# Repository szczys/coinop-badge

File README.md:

# coinop-badge

PCB badge inspired by the classic coin-op game Galaga

https://hackaday.io/project/159302/

# KiCAD Library dependencies

Install the KiCad libraries:
` sudo apt-get install kicad-library

Install the [https://github.com/MacroFab/EDALibraries](MacroFab EDALibraries):
` cd ~/compile
` git clone https://github.com/MacroFab/EDALibraries
` cd /usr/share/kicad/modules 
` sudo ln -s ~/compile/EDALibraries/KiCad/Footprints/* .
` cd /usr/share/kicad/library
` sudo ln -s ~/compile/EDALibraries/KiCad/Schematics/* .

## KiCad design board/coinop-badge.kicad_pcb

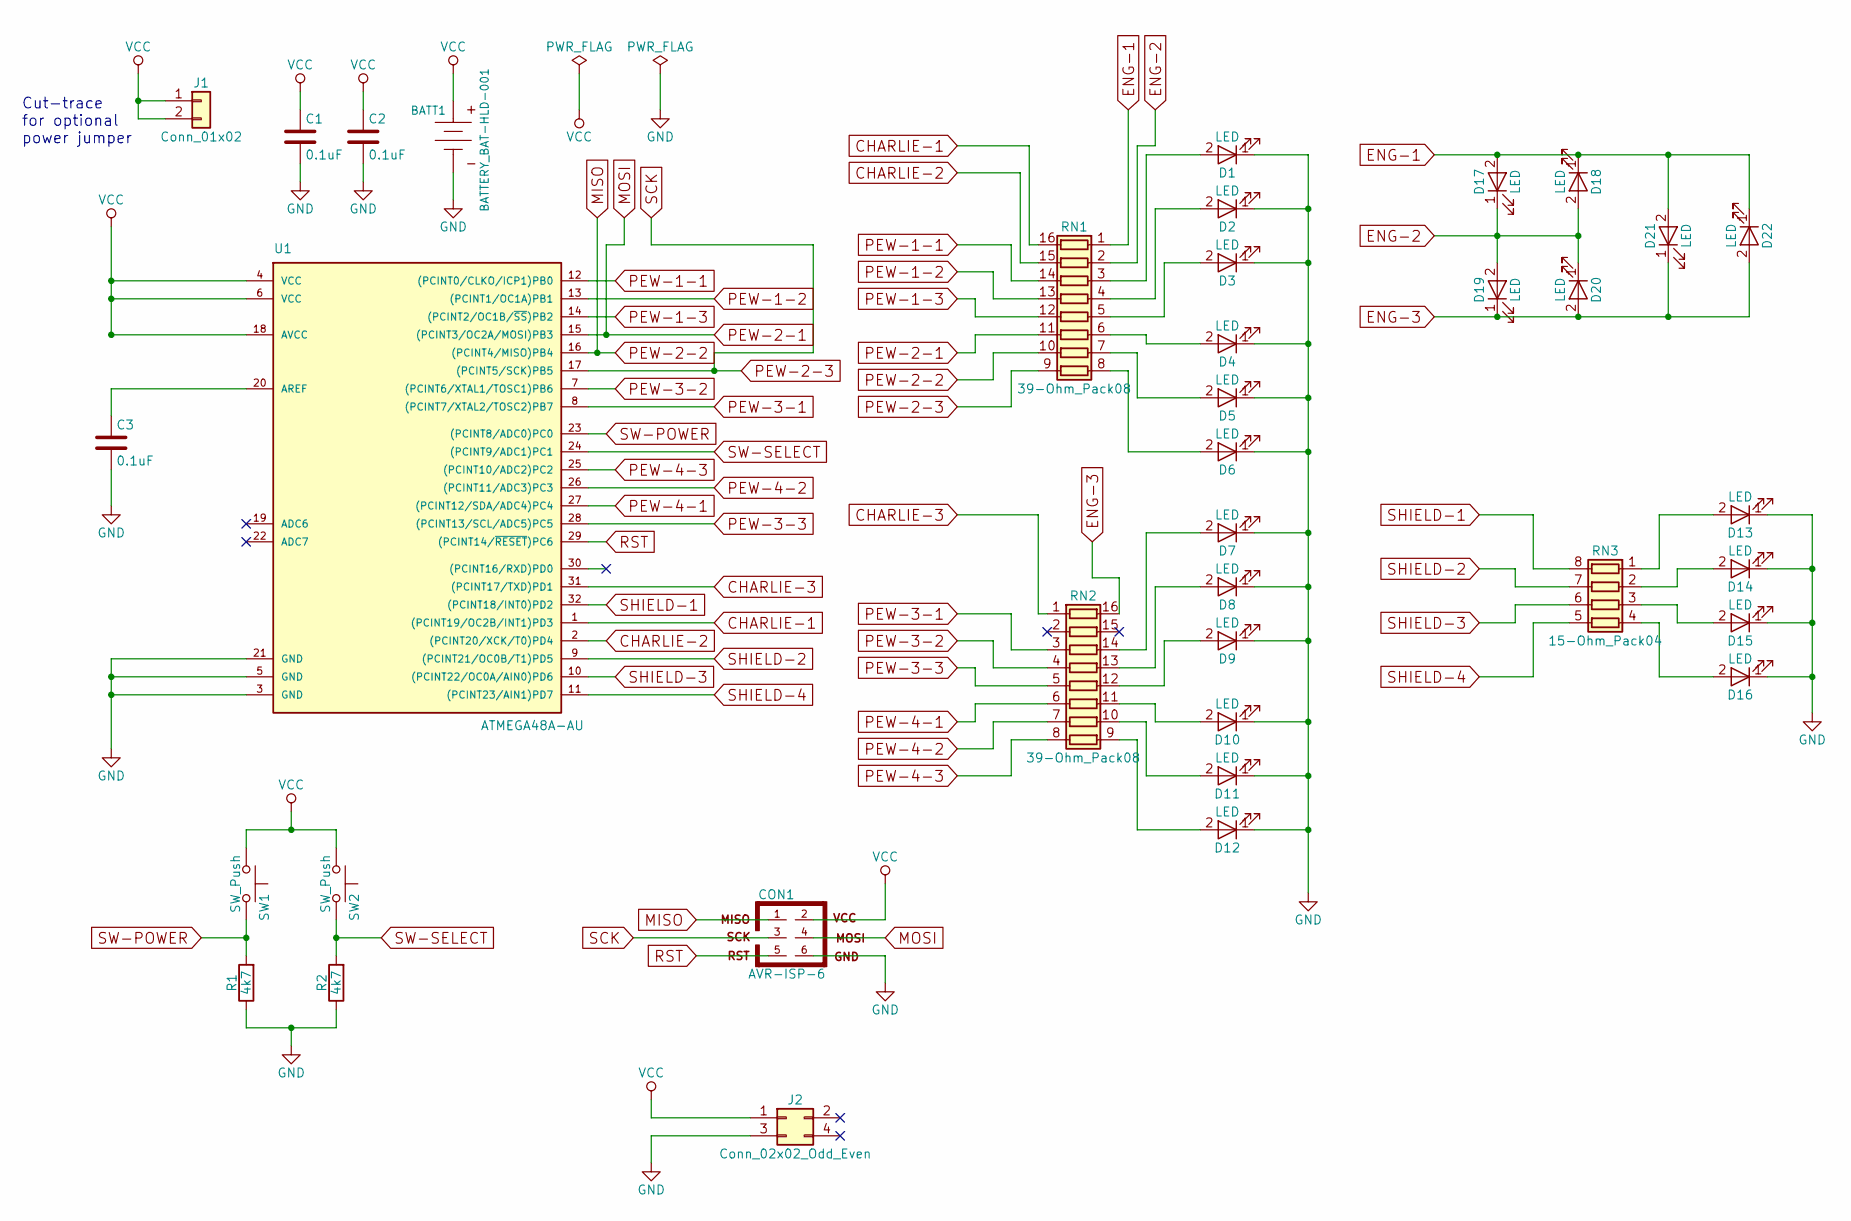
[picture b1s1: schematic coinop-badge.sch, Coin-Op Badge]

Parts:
BATT1: BATTERY_BAT-HLD-001; MF_Connectors-BAT-HLD-001
C1, C2, C3: 0.1uF; LED_0603
CON1: AVR-ISP-6; SIL_1x06_SMD_Pin_Header
D1, D2, D3, D4, D5, D6, D7, D8, D9, D10, D11, D12, D13, D14, D15, D16, D17, D18, D19, D20, D21, D22: LED; LED_0603
J1: Conn_01x02; SIL_1x02_SMD_Pin_Header
J2: Conn_02x02_Odd_Even; SAO_Pin_Header_Straight_2x02_Pitch2.54mm_SMD
R1, R2: 4k7; R_0603
RN1, RN2: 39-Ohm_Pack08; EXB-2HV390JV
RN3: 15-Ohm_Pack04; EXB-38V150JV
SW1, SW2: SW_Push; Switches-TACT-PTS645
U1: ATMEGA48A-AU; TQFP-32_7x7mm_Pitch0.8mm

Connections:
CHARLIE-1: RN1.16 (R1.2), U1.1 ((PCINT19/OC2B/INT1)PD3)
CHARLIE-2: RN1.15 (R2.2), U1.2 ((PCINT20/XCK/T0)PD4)
CHARLIE-3: RN2.1 (R1.1), U1.31 ((PCINT17/TXD)PD1)
ENG-1: D17.2 (A), D18.1 (K), D21.2 (A), D22.1 (K), RN1.1 (R1.1)
ENG-2: D17.1 (K), D18.2 (A), D19.2 (A), D20.1 (K), RN1.2 (R2.1)
ENG-3: D19.1 (K), D20.2 (A), D21.1 (K), D22.2 (A), RN2.16 (R1.2)
GND: BATT1.NEG_ (NEG), C1.2, C2.2, C3.2, CON1.6, D1.1 (K), D2.1 (K), D3.1 (K), D4.1 (K), D5.1 (K), D6.1 (K), D7.1 (K), D8.1 (K), D9.1 (K), D10.1 (K), D11.1 (K), D12.1 (K), D13.1 (K), D14.1 (K), D15.1 (K), D16.1 (K), J2.3, R1.1, R2.1, U1.3 (GND), U1.5 (GND), U1.21 (GND)
MISO: CON1.1, RN1.10 (R7.2), U1.16 ((PCINT4/MISO)PB4)
MOSI: CON1.4, RN1.11 (R6.2), U1.15 ((PCINT3/OC2A/MOSI)PB3)
unnamed: C3.1, U1.20 (AREF)
unnamed: D1.2 (A), RN1.3 (R3.1)
unnamed: D2.2 (A), RN1.4 (R4.1)
unnamed: D3.2 (A), RN1.5 (R5.1)
unnamed: D4.2 (A), RN1.6 (R6.1)
unnamed: D5.2 (A), RN1.7 (R7.1)
unnamed: D6.2 (A), RN1.8 (R8.1)
unnamed: D7.2 (A), RN2.14 (R3.2)
unnamed: D8.2 (A), RN2.13 (R4.2)
unnamed: D9.2 (A), RN2.12 (R5.2)
unnamed: D10.2 (A), RN2.11 (R6.2)
unnamed: D11.2 (A), RN2.10 (R7.2)
unnamed: D12.2 (A), RN2.9 (R8.2)
unnamed: D13.2 (A), RN3.1 (R1.1)
unnamed: D14.2 (A), RN3.2 (R2.1)
unnamed: D15.2 (A), RN3.3 (R3.1)
unnamed: D16.2 (A), RN3.4 (R4.1)
PEW-1-1: RN1.14 (R3.2), U1.12 ((PCINT0/CLKO/ICP1)PB0)
PEW-1-2: RN1.13 (R4.2), U1.13 ((PCINT1/OC1A)PB1)
PEW-1-3: RN1.12 (R5.2), U1.14 ((PCINT2/OC1B/~SS~)PB2)
PEW-2-3: CON1.3, RN1.9 (R8.2), U1.17 ((PCINT5/SCK)PB5)
PEW-3-1: RN2.3 (R3.1), U1.8 ((PCINT7/XTAL2/TOSC2)PB7)
PEW-3-2: RN2.4 (R4.1), U1.7 ((PCINT6/XTAL1/TOSC1)PB6)
PEW-3-3: RN2.5 (R5.1), U1.28 ((PCINT13/SCL/ADC5)PC5)
PEW-4-1: RN2.6 (R6.1), U1.27 ((PCINT12/SDA/ADC4)PC4)
PEW-4-2: RN2.7 (R7.1), U1.26 ((PCINT11/ADC3)PC3)
PEW-4-3: RN2.8 (R8.1), U1.25 ((PCINT10/ADC2)PC2)
RST: CON1.5, U1.29 ((PCINT14/~RESET~)PC6)
SHIELD-1: RN3.8 (R1.2), U1.32 ((PCINT18/INT0)PD2)
SHIELD-2: RN3.7 (R2.2), U1.9 ((PCINT21/OC0B/T1)PD5)
SHIELD-3: RN3.6 (R3.2), U1.10 ((PCINT22/OC0A/AIN0)PD6)
SHIELD-4: RN3.5 (R4.2), U1.11 ((PCINT23/AIN1)PD7)
SW-POWER: R1.2, SW1.2, U1.23 ((PCINT8/ADC0)PC0)
SW-SELECT: R2.2, SW2.2, U1.24 ((PCINT9/ADC1)PC1)
VCC: BATT1.POS_ (POS), C1.1, C2.1, CON1.2, J1.1, J1.2, J2.1, SW1.1, SW2.1, U1.4 (VCC), U1.6 (VCC), U1.18 (AVCC)

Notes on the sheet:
Cut-trace for optional power jumper

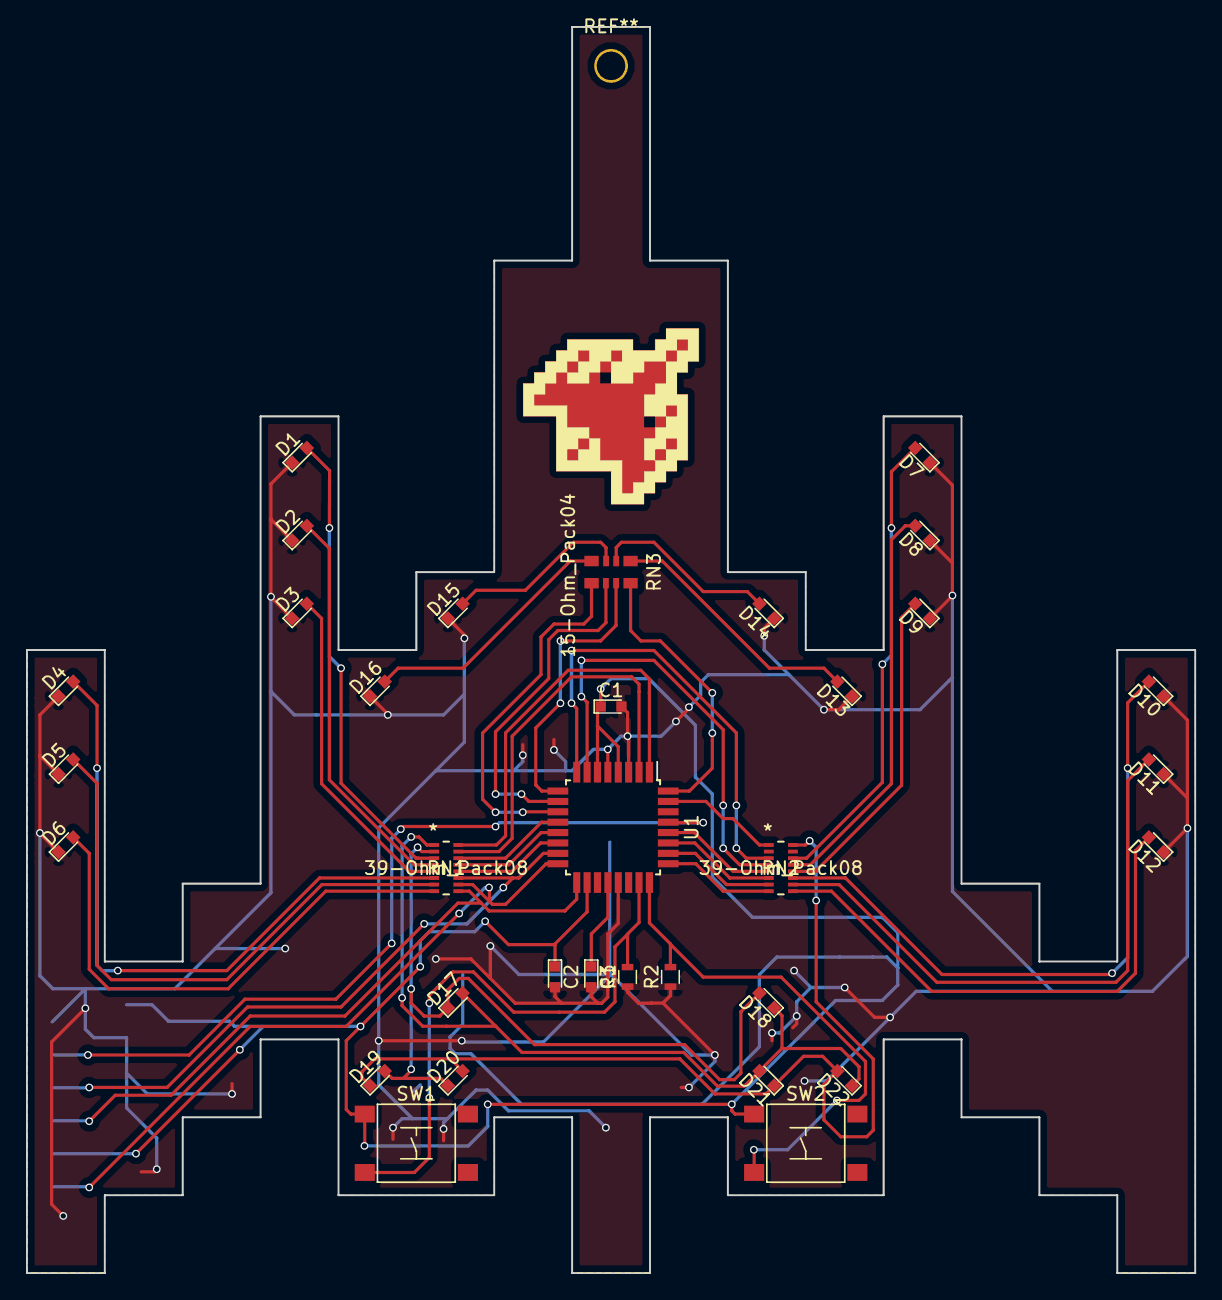
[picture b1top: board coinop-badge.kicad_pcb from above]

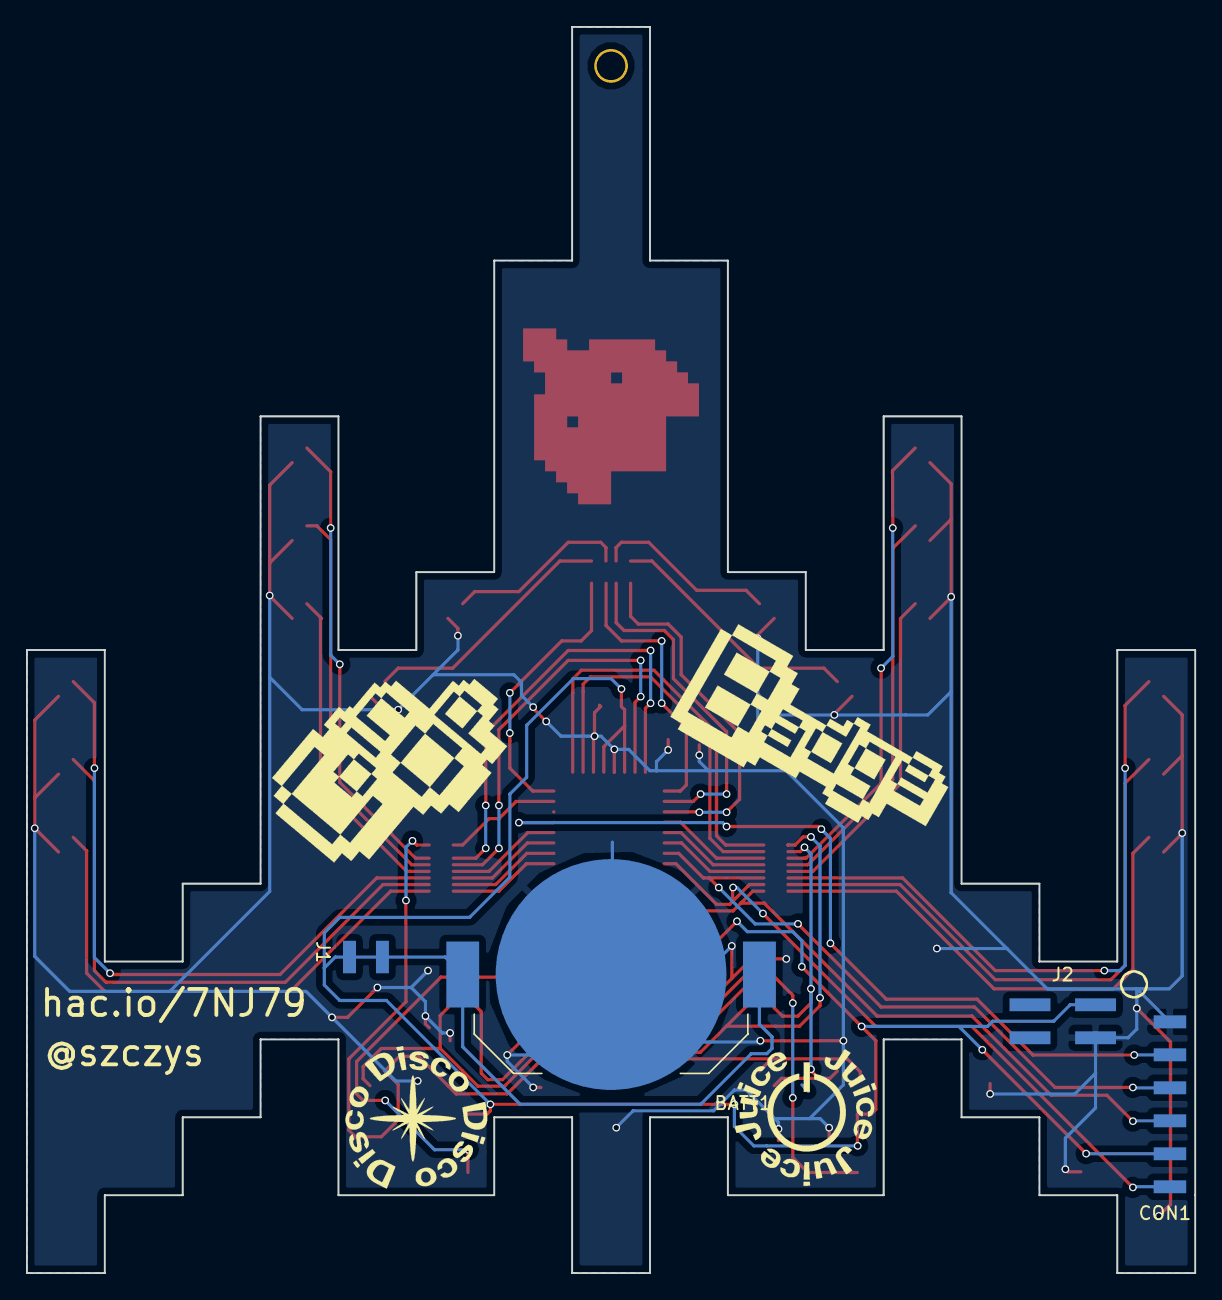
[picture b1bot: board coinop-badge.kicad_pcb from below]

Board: 2 copper layers, 90.0 x 96.0 mm, 37 parts (4 on the bottom side), 44 nets.

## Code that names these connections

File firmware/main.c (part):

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
uint8_t state;

#define PEWLEFTIN1        (1<<PB0)
#define PEWLEFTIN2        (1<<PB1)
#define PEWLEFTIN3        (1<<PB2)
#define PEWLEFTOUT1       (1<<PB3)
#define PEWLEFTOUT2       (1<<PB4)
#define PEWLEFTOUT3       (1<<PB5)
#define PEWRIGHTIN1       (1<<PB7)
#define PEWRIGHTIN2       (1<<PB6)
#define PEWRIGHTIN3       (1<<PC5)
#define PEWRIGHTOUT1      (1<<PC4)
#define PEWRIGHTOUT2      (1<<PC3)
#define PEWRIGHTOUT3      (1<<PC2)

#define SHIELDLEFTOUT     (1<<PD6)
#define SHIELDLEFTIN      (1<<PD7)
#define SHIELDRIGHTOUT    (1<<PD2)
#define SHIELDRIGHTIN     (1<<PD5)

#define CHARLIE1          (1<<PD3)
#define CHARLIE2          (1<<PD4)
#define CHARLIE3          (1<<PD1)

#define OUT_MASK_B        (PEWLEFTIN1 | PEWLEFTIN2 | PEWLEFTIN3 | PEWLEFTOUT1 | PEWLEFTOUT2 | PEWLEFTOUT3 | PEWRIGHTIN1 | PEWRIGHTIN2)
#define OUT_MASK_C        (PEWRIGHTIN3 | PEWRIGHTOUT1 | PEWRIGHTOUT2 | PEWRIGHTOUT3)
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
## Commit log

2018-06-29 initial commit -- board v1.0
2018-06-29 Added project link and library dependencies
2018-07-02 Added schematic frame info Removed incorrect 3D model from edited footprint
2018-07-03 Power on self test code (untested)
2018-07-04 Post now passes as a pointer Charlieplexing clears port bits before driving
2018-07-04 Removed erroneous connection left over from larger charlieplex array
2018-07-04 Added sleep mode and PCINT. Working well but code needs clean up
2018-07-04 Added debounce FIXME: debouncing the button for sleep requires double click before second sleep mode cycle is entered. Bizarre
2018-07-04 Debounced buttons are now working to enter sleep mode
2018-07-04 Moved Timer0 to 1ms to use as non-blocking delay value
2018-07-04 Made POST nonblocking FIXME: POST stops with last charlieplexed LED still lit
2018-07-04 Fixed charliexplex handling in post()
2018-07-05 Empty ISR is required; without it there's a jumpt to reset
2018-07-07 Fixed: PCINT flag wasn't being cleared after wake Fixed: Maping error in POST Added: Charlieplexing via TIMER1 (commented out the interrupt enable though) Updated: Clock speed and chip value for ATme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
2018-07-07 Implemented scanning (no duty cycle yet)
2018-07-07 Fixed routing mistake on buttons. Board now at v2
2018-07-07 Added 4 level PWM
2018-07-07 Addded 16 stages of fading (multiplexed 6 was so 96 steps)
2018-07-07 Added spinning engine lights to the bling
2018-07-08 Abstracted out the pulsate animation
2018-07-08 Added pew visualization
2018-07-08 Setting up proper state change system
2018-07-08 Buttons fire lasers
2018-07-08 Added disco-button hold for state increment
2018-07-08 Abstracted button handling into separate file
2018-07-08 Added prototpye and tweake repeat timing
2018-07-08 Better state handling Tweks to PEW visualization
2018-07-08 Changed size display format
2018-07-08 Added sparkly visualization Implemented repeated patterns followed by state change
2018-07-08 Optimized post()
2018-07-09 Fixed overflow in sparkle()
2018-07-09 Cleaning up and getting organized
2018-07-09 Added low-power sleep between visualizations (WDT or PCINT to wake)
2018-07-09 Added ability for buttons to fire lasers one at a time
2018-07-09 Added shield behavior but it's kinda crap so will likely get rid of it
2018-07-10 Modified support for manual lasers
2018-07-10 Woking through hairy button reads (avoiding spurious presses when waking or repeating)
2018-07-10 Added power down sequence FIXME: Power keypress is happening immediately after wakeup
2018-07-10 Fixed spurious button presses in power down sequence
2018-07-14 Working out button handling
2018-07-15 Button behavior now stable
2018-07-15 Add sweeper visualization
2018-07-15 Added 90-minute hard sleep timer if no buttons are pushed
2018-07-15 Fixed button routing error Added SAO header (wired as add-on, not host) Added button labels
2018-07-15 Abstracted timers and step counters into a struct
2018-07-15 Cleaning up prototypes
2018-07-15 Saved some space by combining laser functions
2018-07-15 Saved space by combining left and right turret code
2018-07-15 Fixed missing dereference operator
2018-07-15 Added animtion to the pew state
2018-07-15 Added shields and engines to animated pew
2018-07-16 Fixed pew animation ending
2018-07-20 Added (commented out) line with fuse burning command. Use with caution
2018-07-31 Ignore disco button during power up and power down confirmations
2018-08-05 Added way to break loop in wake cheack (prevent false readings that wake the uC)
2018-08-05 Added production hex file for v1.3

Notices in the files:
parts and their libraries:
Copyright 2016 Accelerated Designs. All rights reserved.
